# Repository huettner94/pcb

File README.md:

# PCB

Repo of all random PCBs that i have built

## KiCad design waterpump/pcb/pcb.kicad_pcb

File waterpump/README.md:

# Waterpump PCB

This is a PCB for a waterpump controller using esphome.

This controller works with a 12V power supply for the Pump and does the necessary step down conversion on the board.
The components would also be able to handle 24V if needed for the pump.

The 74HCT is completely overkill, but i had it laying around.

## Components

| Name | Place on PCB | example link |
|------|--------------|--------------|
| D1 Mini | U1 | [here](https://www.reichelt.de/d1-mini-kompatibles-esp8266-board-v2-0-d1-mini-p253978.html) |
| 74HCT 245 | U2 | [here](https://www.digikey.de/de/products/detail/texas-instruments/SN74HCT245N/277258) potentially with a [socket](https://www.digikey.de/de/products/detail/on-shore-technology-inc/ED20DT/4147598) |
| Screw Connectorx | J1, J2, J3, J4, J5 | e.g. [this](https://www.digikey.de/de/products/detail/molex/0397730002/9740839) but at reichelt a lot cheaper [here](https://www.reichelt.de/de/de/shop/produkt/anschlussklemme_2-pol_2_mm_rm_5_08-36605) |
| Relay AZ943-1CH-5DE | K1 | [here](https://www.digikey.de/de/products/detail/american-zettler/AZ943-1CH-5DE/14307553) |
| Polyfuse 30V 1A | F1 | [here](https://www.digikey.de/de/products/detail/bourns-inc/MF-R110/259970) |
| Polyfuse 6V 1A | F2 | [here](https://www.digikey.de/de/products/detail/littelfuse-inc/RUSBF120-2/5029818) |
| Resistor 4.7k | R1 | [here](https://www.digikey.de/de/products/detail/stackpole-electronics-inc/CF18JT4K70/1741708) |
| Resistor 5.1k | R2 | |
| LED WP7113ID | D1 | [here](https://www.digikey.de/de/products/detail/kingbright/WP7113ID/1747663) |
| Capacitor 35V 1500uF | C1 | [here](https://www.digikey.de/de/products/detail/rubycon/35ZLH1500MEFC16X20/3564410) |
| Capacitor 24V 1uF | C2 | [here](https://www.digikey.de/de/products/detail/w%C3%BCrth-elektronik/860020672005/5727088) |
| Capacitor 5V 10uF | C3, C4 | [here](https://www.digikey.de/de/products/detail/w%C3%BCrth-elektronik/860010472002/5726873) |
| Step down converter MEZD71201A-G | J6 | [here](https://www.digikey.de/de/products/detail/monolithic-power-systems-inc/MEZD71201A-G/6823821) |
| Step down converter socket | J6 | e.g. [here](https://www.digikey.de/de/products/detail/sullins-connector-solutions/PPTC031LFBN-RC/810143) |

For power supply i used a bunch of AA batteries.

The pump is a Blanko 38-06. E.g. from [Amazon](https://www.amazon.de/Noname-Universelle-Wasserpumpe-Pumpe-min/dp/B002WZM3II/ref=cm_cr_srp_d_product_top?ie=UTF8).

## Instructions

1. Solder everything together
2. install esphome and configure it with GPIO5 for the output
3. Have fun

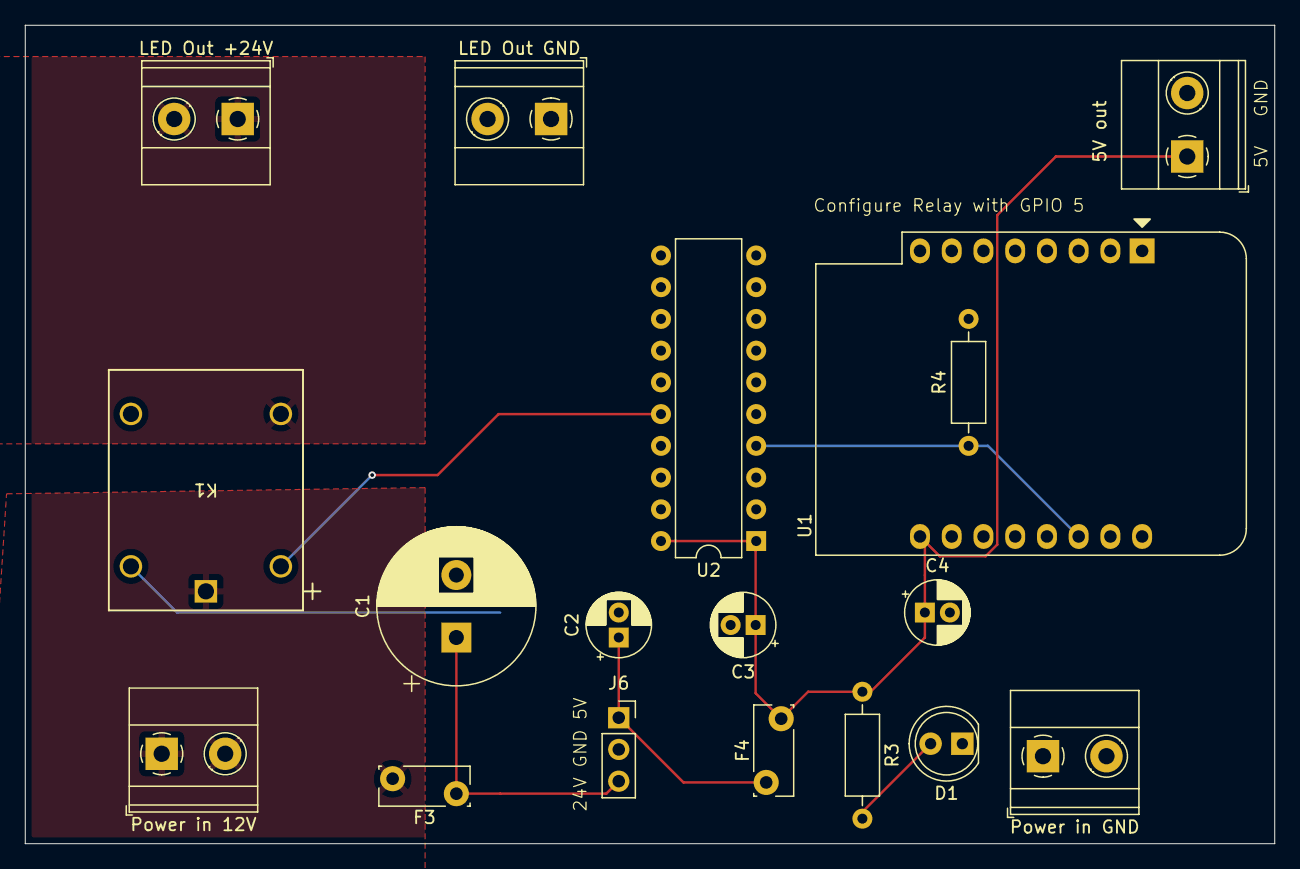
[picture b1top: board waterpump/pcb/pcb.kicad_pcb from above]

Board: 2 copper layers, 100.0 x 65.5 mm, 18 parts (0 on the bottom side), 11 nets.

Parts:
C1: C 1500uF 24V; CP_Radial_D12.5mm_P5.00mm
C2: C 1uF 24V; CP_Radial_D5.0mm_P2.00mm
C3: C 10uF 5V optional (nah an level shifter); CP_Radial_D5.0mm_P2.00mm
C4: C 10uF 5V optional (nah an esp); CP_Radial_D5.0mm_P2.00mm
D1: LED WP7113ID; LED_D5.0mm
F3: Polyfuse 30V 1A; Fuse_Bourns_MF-RG300
F4: Polyfuse 6V 1A; Fuse_Bourns_MF-RG300
J1: LED Out +24V; TerminalBlock_Phoenix_MKDS-1,5-2-5.08_1x02_P5.08mm_Horizont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
J3: LED Out GND; TerminalBlock_Phoenix_MKDS-1,5-2-5.08_1x02_P5.08mm_Horizont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
J4: 5V out; TerminalBlock_Phoenix_MKDS-1,5-2-5.08_1x02_P5.08mm_Horizont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
J5: Power in 12V; TerminalBlock_Phoenix_MKDS-1,5-2-5.08_1x02_P5.08mm_Horizont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
J6: MEZD71201A-G; PinSocket_1x03_P2.54mm_Vertical
J7: Power in GND; TerminalBlock_Phoenix_MKDS-1,5-2-5.08_1x02_P5.08mm_Horizont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
K1: AZ943-1CH-5DE; K_AZ943-1C_AMZ
R3: R 4k7; R_Axial_DIN0207_L6.3mm_D2.5mm_P10.16mm_Horizontal
R4: R 5.1k; R_Axial_DIN0207_L6.3mm_D2.5mm_P10.16mm_Horizontal
U1: WLED; WEMOS_D1_mini_light
U2: 74HCT245; DIP-20_W7.62mm

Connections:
+5VD: C3.1, C4.1, F4.2, J4.1, R3.1, U1.9 (5V), U2.1 (A->B), U2.20 (VCC)
+12V: F3.2, J5.1, J5.2, K1.1
+12V after Relay: J1.1, J1.2, K1.3
GND: C1.2, C2.2, C3.2, C4.2, D1.1 (K), J3.1, J3.2, J4.2, J6.2, J7.1, J7.2, K1.5, R4.2, U1.10 (GND), U2.10 (GND), U2.19 (CE)
unnamed: D1.2 (A), R3.2
unnamed: C2.1, F4.1, J6.1
unnamed: C1.1, F3.1, J6.3
unnamed: U1.11 (D4), U2.3 (A1)
unnamed: R4.1, U1.14 (SCL/D1), U2.4 (A2)
unnamed: U1.16 (TX), U2.2 (A0)
unnamed: K1.2, U2.16 (B2)

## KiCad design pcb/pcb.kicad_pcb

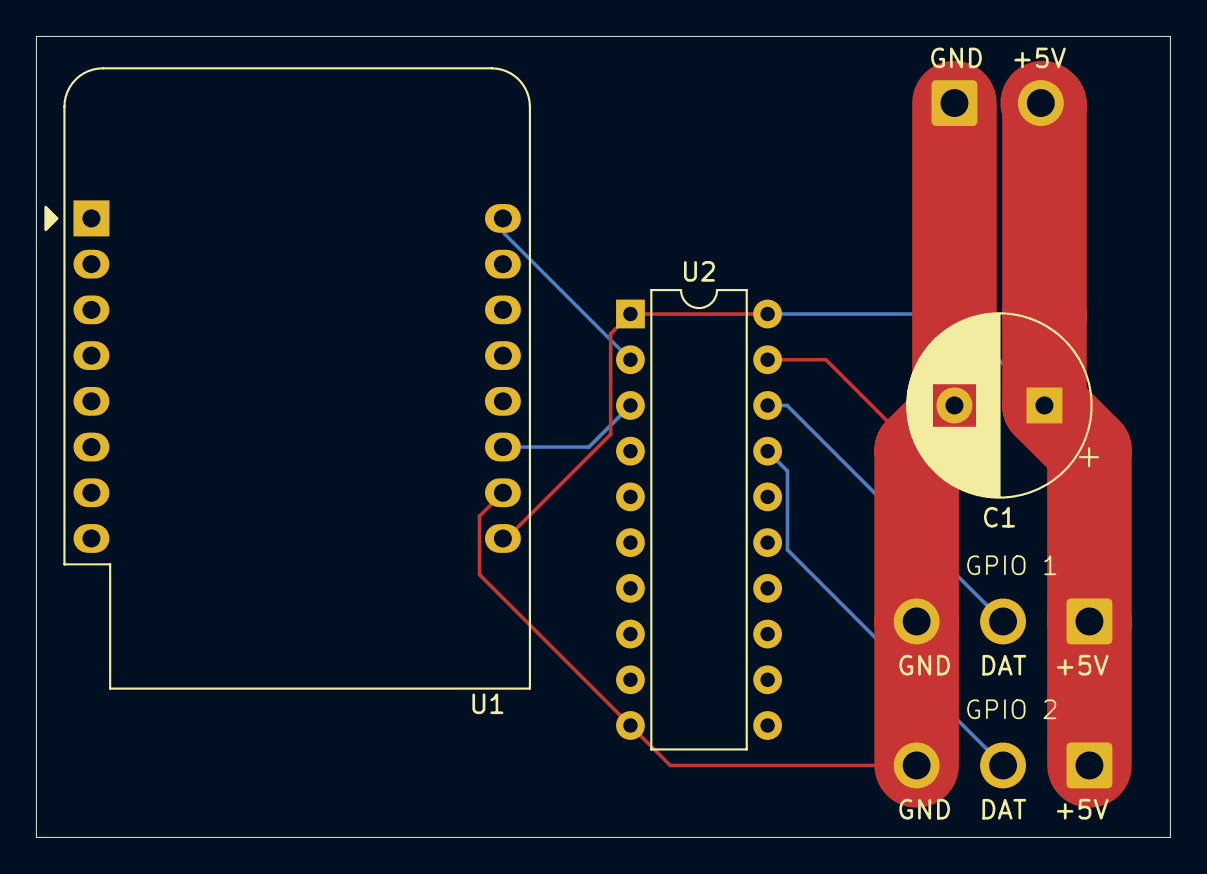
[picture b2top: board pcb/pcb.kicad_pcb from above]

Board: 2 copper layers, 63.0 x 44.5 mm, 6 parts (0 on the bottom side), 6 nets.

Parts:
C1: 1000µF; CP_Radial_D10.0mm_P5.00mm
GND  +5V: Conn_01x02_Socket; SolderWire-0.75sqmm_1x02_P4.8mm_D1.25mm_OD2.3mm
GND  DAT  +5V, GND  DAT  +5V#2: Conn_01x03_Socket; SolderWire-0.75sqmm_1x03_P4.8mm_D1.25mm_OD2.3mm
U1: WeMos_D1_mini; WEMOS_D1_mini_light
U2: 74HCT245; DIP-20_W7.62mm

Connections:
+5VD: C1.1, GND +5V.2, GND DAT +5V.1, GND DAT +5V#2.1, U1.9 (5V), U2.1 (A->B), U2.20 (VCC)
GND: C1.2, GND +5V.1, GND DAT +5V.3, GND DAT +5V#2.3, U1.10 (GND), U2.10 (GND), U2.19 (CE)
unnamed: GND DAT +5V#2.2, U2.18 (B0)
unnamed: GND DAT +5V.2, U2.17 (B1)
unnamed: U1.11 (D4), U2.3 (A1)
unnamed: U1.16 (TX), U2.2 (A0)

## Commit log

2024-09-13 add case idea
2024-09-15 add some general description
2024-09-15 add real case
2025-02-07 add extended pcb
2025-02-07 add case
2025-02-21 fix relay flickering on boot
2025-03-02 This commit is most probably wrong, but lets store it
    The issue is that when the PCB is provided power then the led strip
    quickly lights up, then goes of. Afterwards wled turns it on again.
    I though this is because the wiring of the relay is wrong. The
    documentation shows the default state to be in reverse of what the
    downloadbale schematic provides
    (https://www.azettler.com/pdfs/az943.pdf).
2025-03-06 update kicad
2025-03-07 add missing pulldown resistor
    D1 does not have a pulldown resistor included, so the output is floating
    during boot. This can cause the led strip to flicker.
    Fix this by adding a pulldown resistor.
2025-05-18 rename repo
2025-05-18 add pump pcb
